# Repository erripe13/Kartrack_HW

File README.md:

# Kartrak – Hardware

> **Dépôts associés** :  
> - [Kartrack_SW](https://github.com/erripe13/Kartrack_SW) – Code embarqué STM32 (FreeRTOS, GPS, LoRa, SD...)  
> - [Kartrack_HW](https://github.com/erripe13/Kartrack_HW) – **Ce dépôt** – Schéma et PCB du système  
> - [Kartrack_APP](https://github.com/erripe13/Kartrack_APP) – Application d’analyse et visualisation des données

## Présentation du projet Kartrak

Kartrak est un système embarqué de chronométrage et de télémétrie pour karting, conçu pour être fixé sur le volant. Il enregistre en temps réel les données de course (position GPS, accélérations, orientation) et les transmet en LoRa à l'appli desktop et les enregistre sur carte microSD. L’objectif est de proposer un outil complet pour les pilotes amateurs ou en compétition : analyse post-course, visualisation en temps réel par l'équipe, appel aux stands, comparaisons de trajectoires.

---

Le projet est basé sur la plateforme **STM32F746G-DISCO**, exploitant son STM32 puissant et ses périphériques avancés (écran TFT, SDMMC, i2c, SPI, UART) pour accélérer le développement hardware, éliminant l'étape d'implémentation écran/uC.

Ce dépôt contient les fichiers **KiCad** du schéma électronique et du circuit imprimé (PCB) conçu pour le système embarqué Kartrack. Il s’agit d’une carte d’interface et d’alimentation destinée à supporter la carte **STM32F746G-DISCO** tout en intégrant les composants spécifiques au projet.

Le système est alimenté à partir de **deux batteries 18650** montées en **parallèle**. Un **convertisseur boost (step-up)** élève la tension à 5 V pour alimenter la carte STM32F7 Discovery via ses broches VIN (arduino) et GND. Ces 5V sont réutilisés et abaissés à 3.3V avec un LDO. Un autre LDO permet la recharge des batteries.

Le PCB a été conçu dans une logique de prototypage rapide :
- **Réduction du temps de conception** en réutilisant une carte STM32 existante (la DISCO) plutôt qu’un microcontrôleur nu.
- Embarque les modules suivants :
  - LoRa : RA-01 (SPI). Le Lora nous permet de couvrir un grand espace de communication (Piste de Karting) sans passer par le réseau GSM et a aussi l'a avantage d'une faible consommation électrique.
  - GPS : Quectel L76 (UART). Le grand avantage de ce GPS est sa fréquence élevée d'acquisition, ici 5Hz. La norme des GPS est de 1Hz, mais pour un kart à 60km/h sur une piste de 1000m la norme n'est pas suffisante.
  - IMU : ICM-42605 (I²C). L'accéléromètre et le gyroscope nous permettent d'ajouter une donnée en plus à notre pilote. Ici le gyro est réglé sur la mesure la plus rapide, et l'accélaration la plus élevée (16G). En cas d'accident par exemple cette donnée peut être des plus intéressantes.  
     
---

## À venir

- Intégration directe d’un STM32 nu sur une version 1 de ce projet, considérant celle-ci comme une bêta ou un POC.
- Création d'un boîtier en conséquence plus fin et plus petit, potentiellement étanche.
- Amélioration de la partie RF pour une meilleure fiabilité du GPS et une plus grande portée du LoRa.

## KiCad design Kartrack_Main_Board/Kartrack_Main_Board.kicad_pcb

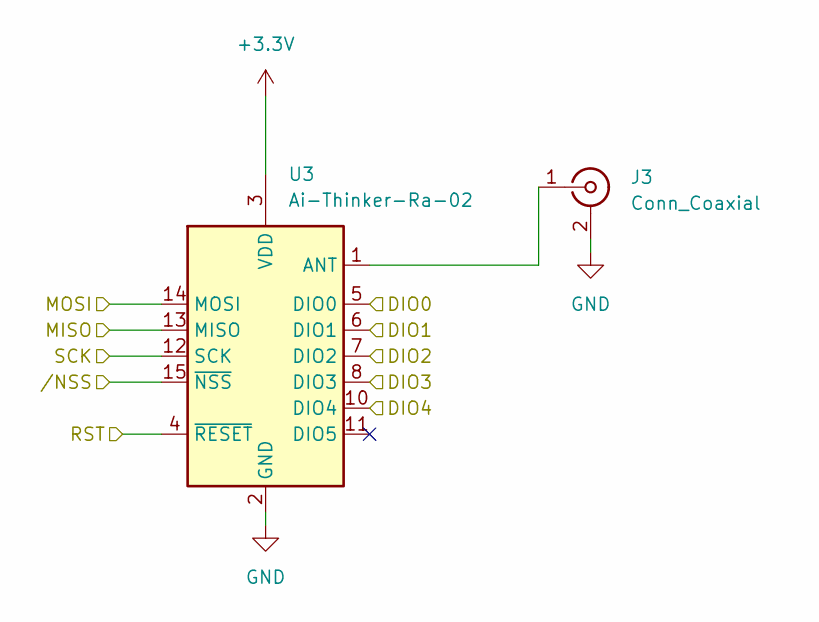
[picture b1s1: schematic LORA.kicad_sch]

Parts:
J3: Conn_Coaxial; U.FL_Molex_MCRF_73412-0110_Vertical
U3: Ai-Thinker-Ra-02; Ai-Thinker-Ra-01-LoRa

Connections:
+3.3V: U3.3 (VDD); also elsewhere on the board
/CONN/PA8: U3.8 (DIO3); also elsewhere on the board
/CONN/PA15: U3.7 (DIO2); also elsewhere on the board
/CONN/PB4: U3.10 (DIO4); also elsewhere on the board
/CONN/PB14_SPI2_MISO: U3.13 (MISO); also elsewhere on the board
/CONN/PB15_SPI2_MOSI: U3.14 (MOSI); also elsewhere on the board
/CONN/PF8_LORA_RST: U3.4 (~RESET); also elsewhere on the board
/CONN/PI1_SPI2_SCK: U3.12 (SCK); also elsewhere on the board
/CONN/PI2: U3.6 (DIO1); also elsewhere on the board
/CONN/PI3: U3.5 (DIO0); also elsewhere on the board
/CONN/PIO_SPI2_NSS: U3.15 (~NSS); also elsewhere on the board
GND: J3.2 (Ext), U3.2 (GND), U3.9 (GND), U3.16 (GND); also elsewhere on the board
unnamed: J3.1 (In), U3.1 (ANT)

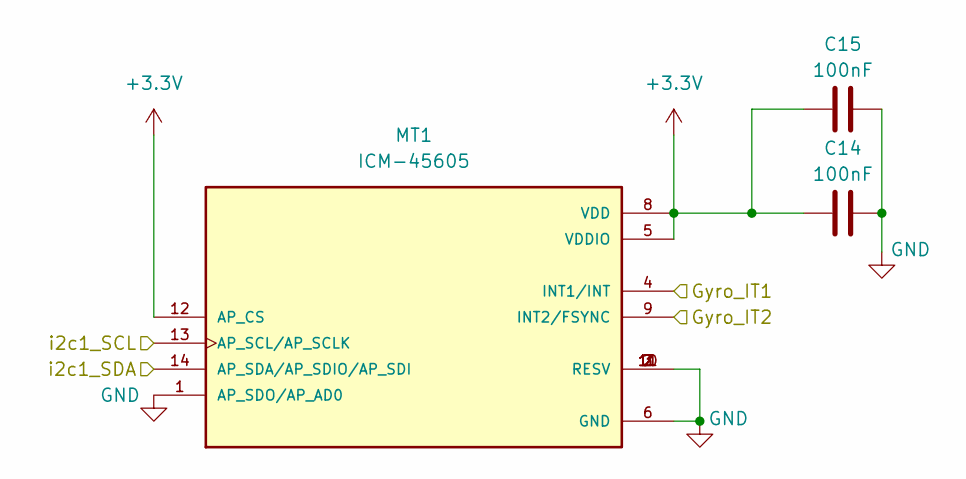
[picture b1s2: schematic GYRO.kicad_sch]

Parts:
C14, C15: 100nF; C_0402_1005Metric
MT1: ICM-45605; IC_ICM-45605; PARTREV 1.7

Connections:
+3.3V: C14.1, C15.1, MT1.5 (VDDIO), MT1.8 (VDD), MT1.12 (AP_CS); also elsewhere on the board
/CONN/PB8_SCL: MT1.13 (AP_SCL/AP_SCLK); also elsewhere on the board
/CONN/PB9_SDA: MT1.14 (AP_SDA/AP_SDIO/AP_SDI); also elsewhere on the board
/CONN/PF6: MT1.9 (INT2/FSYNC); also elsewhere on the board
/CONN/PG7: MT1.4 (INT1/INT); also elsewhere on the board
GND: C14.2, C15.2, MT1.1 (AP_SDO/AP_AD0), MT1.2 (RESV), MT1.3 (RESV), MT1.6 (GND), MT1.7 (RESV), MT1.10 (RESV), MT1.11 (RESV); also elsewhere on the board

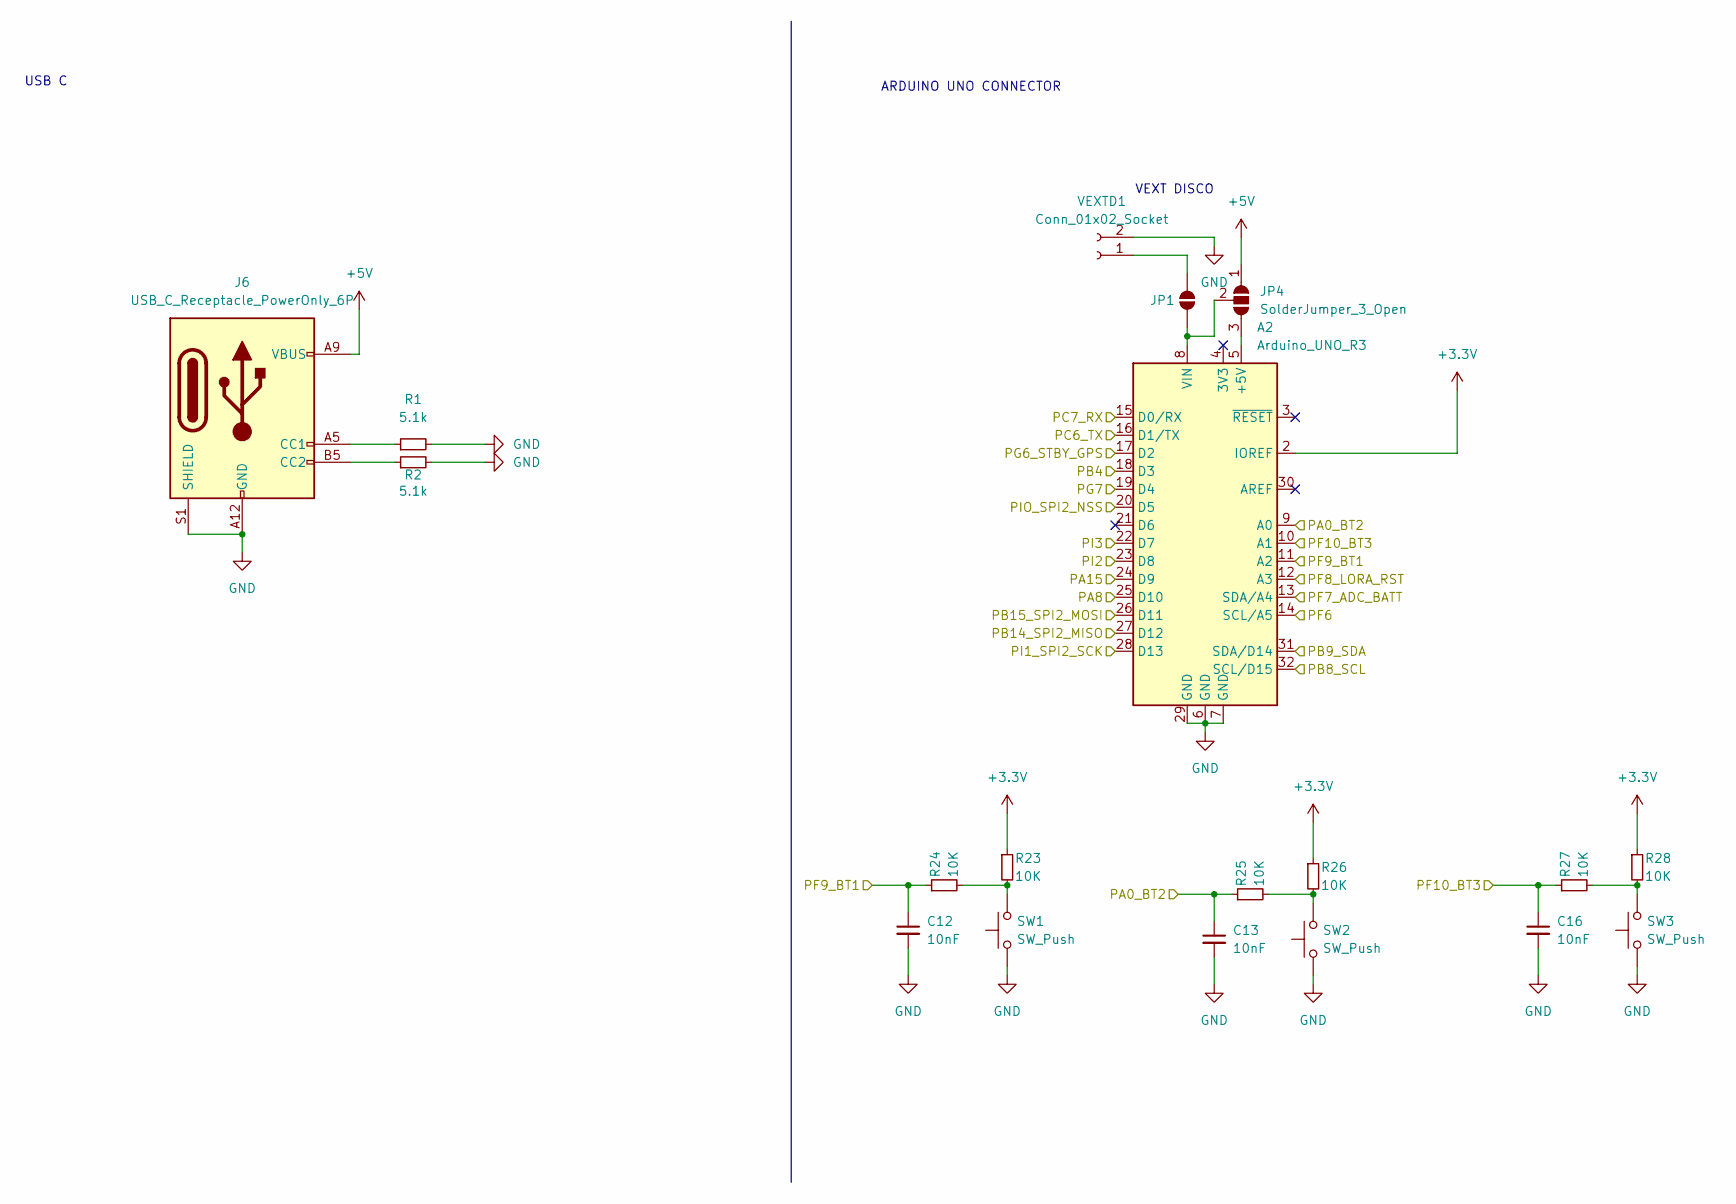
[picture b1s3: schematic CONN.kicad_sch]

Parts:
A2: Arduino_UNO_R3
C12, C13, C16: 10nF; C_0603_1608Metric
J6: USB_C_Receptacle_PowerOnly_6P; USB_C_Receptacle_GCT_USB4125-xx-x_6P_TopMnt_Horizontal
JP1: SolderJumper_2_Open; SolderJumper-2_P1.3mm_Open_RoundedPad1.0x1.5mm
JP4: SolderJumper_3_Open; SolderJumper-3_P2.0mm_Open_TrianglePad1.0x1.5mm_NumberLabels
R1, R2: 5.1k; R_0603_1608Metric
R23, R24, R25, R26, R27, R28: 10K; R_0603_1608Metric
SW1, SW2, SW3: SW_Push; JST_PH_S2B-PH-K_1x02_P2.00mm_Horizontal
VEXTD1: Conn_01x02_Socket; PhoenixContact_MC_1,5_2-G-3.81_1x02_P3.81mm_Horizontal

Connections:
+3.3V: A2.2 (IOREF), R23.1, R26.1, R28.1; also elsewhere on the board
+5V: J6.A9 (VBUS), J6.B9 (VBUS), JP4.1 (A); also elsewhere on the board
/ALIM/ADC_VBATT: A2.13 (SDA/A4); also elsewhere on the board
/CONN/PA0_BT2: A2.9 (A0), C13.1, R25.1
/CONN/PA8: A2.25 (D10); also elsewhere on the board
/CONN/PA15: A2.24 (D9); also elsewhere on the board
/CONN/PB4: A2.18 (D3); also elsewhere on the board
/CONN/PB8_SCL: A2.32 (SCL/D15); also elsewhere on the board
/CONN/PB9_SDA: A2.31 (SDA/D14); also elsewhere on the board
/CONN/PB14_SPI2_MISO: A2.27 (D12); also elsewhere on the board
/CONN/PB15_SPI2_MOSI: A2.26 (D11); also elsewhere on the board
/CONN/PC6_TX: A2.16 (D1/TX); also elsewhere on the board
/CONN/PC7_RX: A2.15 (D0/RX); also elsewhere on the board
/CONN/PF6: A2.14 (SCL/A5); also elsewhere on the board
/CONN/PF8_LORA_RST: A2.12 (A3); also elsewhere on the board
/CONN/PF9_BT1: A2.11 (A2), C12.1, R24.1
/CONN/PF10_BT3: A2.10 (A1), C16.1, R27.1
/CONN/PG6_STBY_GPS: A2.17 (D2); also elsewhere on the board
/CONN/PG7: A2.19 (D4); also elsewhere on the board
/CONN/PI1_SPI2_SCK: A2.28 (D13); also elsewhere on the board
/CONN/PI2: A2.23 (D8); also elsewhere on the board
/CONN/PI3: A2.22 (D7); also elsewhere on the board
/CONN/PIO_SPI2_NSS: A2.20 (D5); also elsewhere on the board
GND: A2.6 (GND), A2.7 (GND), A2.29 (GND), C12.2, C13.2, C16.2, J6.A12 (GND), J6.B12 (GND), J6.S1 (SHIELD), R1.2, R2.2, SW1.1, SW2.1, SW3.1, VEXTD1.2; also elsewhere on the board
unnamed: A2.5 (+5V), JP4.3 (B)
unnamed: A2.8 (VIN), JP1.1 (A), JP4.2 (C)
unnamed: J6.A5 (CC1), R1.1
unnamed: J6.B5 (CC2), R2.1
unnamed: JP1.2 (B), VEXTD1.1
unnamed: R23.2, R24.2, SW1.2
unnamed: R25.2, R26.2, SW2.2
unnamed: R27.2, R28.2, SW3.2

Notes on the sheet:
USB C
ARDUINO UNO CONNECTOR
VEXT DISCO

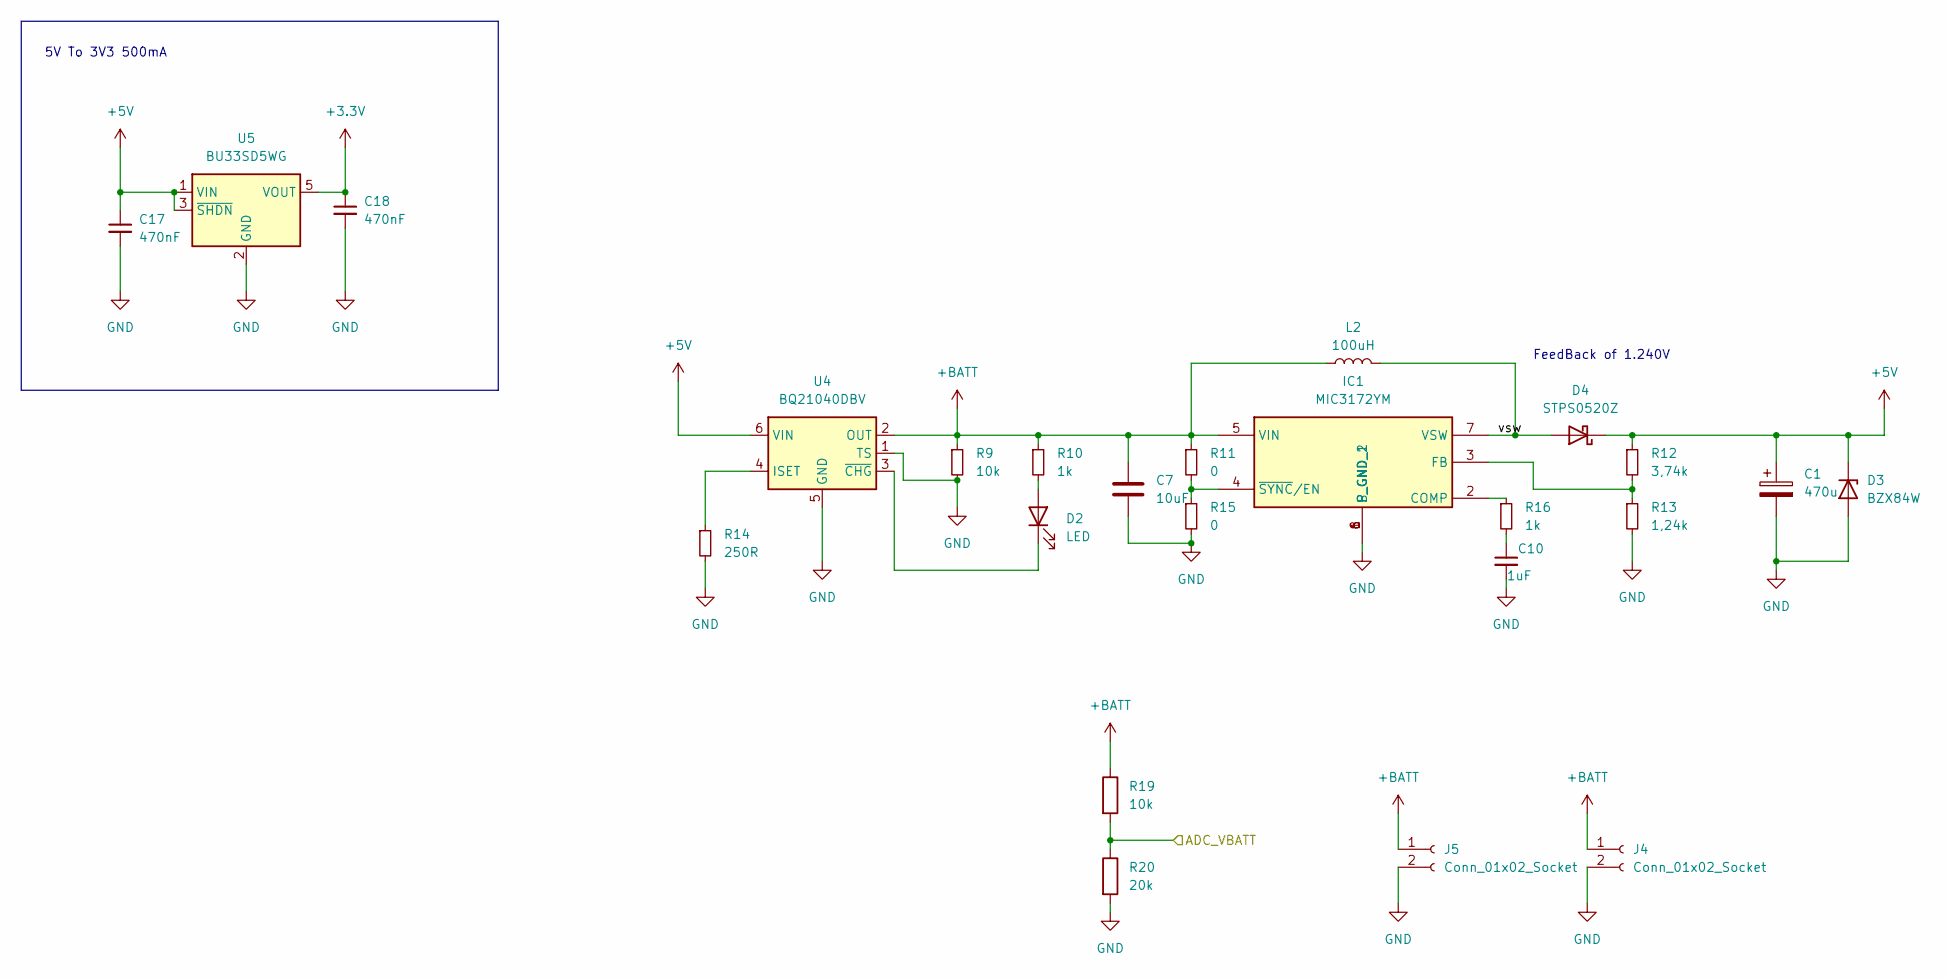
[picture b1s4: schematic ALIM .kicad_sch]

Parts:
C1: 470u; CP_Elec_8x10
C7: 10uF; C_0603_1608Metric
C10: 1uF; C_0603_1608Metric
C17, C18: 470nF; C_0603_1608Metric
D2: LED; LED_0603_1608Metric
D3: BZX84W; SOT-23
D4: STPS0520Z; D_SOD-123
IC1: MIC3172YM; SOIC127P599X173-8N; MPN MIC3172YM; Mouser Part Number 998-MIC3172YM
J4, J5: Conn_01x02_Socket; BatteryHolder_MPD_BH-18650-PC2
L2: 100uH; L_12x12mm_H8mm
R9, R19: 10k; R_0603_1608Metric
R10, R16: 1k; R_0603_1608Metric
R11, R15: 0; R_0603_1608Metric
R12: 3,74k; R_0603_1608Metric; MPN CRCW06033K74DHEAP
R13: 1,24k; R_0603_1608Metric; MPN CRCW06031K24FKEAHP
R14: 250R; R_0603_1608Metric
R20: 20k; R_0603_1608Metric
U4: BQ21040DBV; SOT-23-6; MPN BQ21040DBVR
U5: BU33SD5WG; SOT-23-5; MPN BU33SD5WG-TR

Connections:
+3.3V: C18.1, U5.5 (VOUT); also elsewhere on the board
+5V: C1.1, C17.1, D3.3 (K), D4.1 (K), R12.1, U4.6 (VIN), U5.1 (VIN), U5.3 (~SHDN); also elsewhere on the board
+BATT: C7.1, IC1.5 (VIN), J4.1, J5.1, L2.1, R9.1, R10.1, R11.1, R19.1, U4.2 (OUT)
/ALIM/ADC_VBATT: R19.2, R20.1; also elsewhere on the board
/ALIM/vsw: D4.2 (A), IC1.7 (VSW), L2.2
GND: C1.2, C7.2, C10.2, C17.2, C18.2, D3.1 (A), IC1.1 (S_GND), IC1.6 (P_GND_2), IC1.8 (P_GND_1), J4.2, J5.2, R9.2, R13.2, R14.2, R15.2, R20.2, U4.1 (TS), U4.5 (GND), U5.2 (GND); also elsewhere on the board
unnamed: C10.1, R16.2
unnamed: D2.2 (A), R10.2
unnamed: D2.1 (K), U4.3 (~CHG)
unnamed: IC1.2 (COMP), R16.1
unnamed: IC1.3 (FB), R12.2, R13.1
unnamed: IC1.4 (~SYNC/EN), R11.2, R15.1
unnamed: R14.1, U4.4 (ISET)

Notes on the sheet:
5V To 3V3 500mA
FeedBack of 1.240V

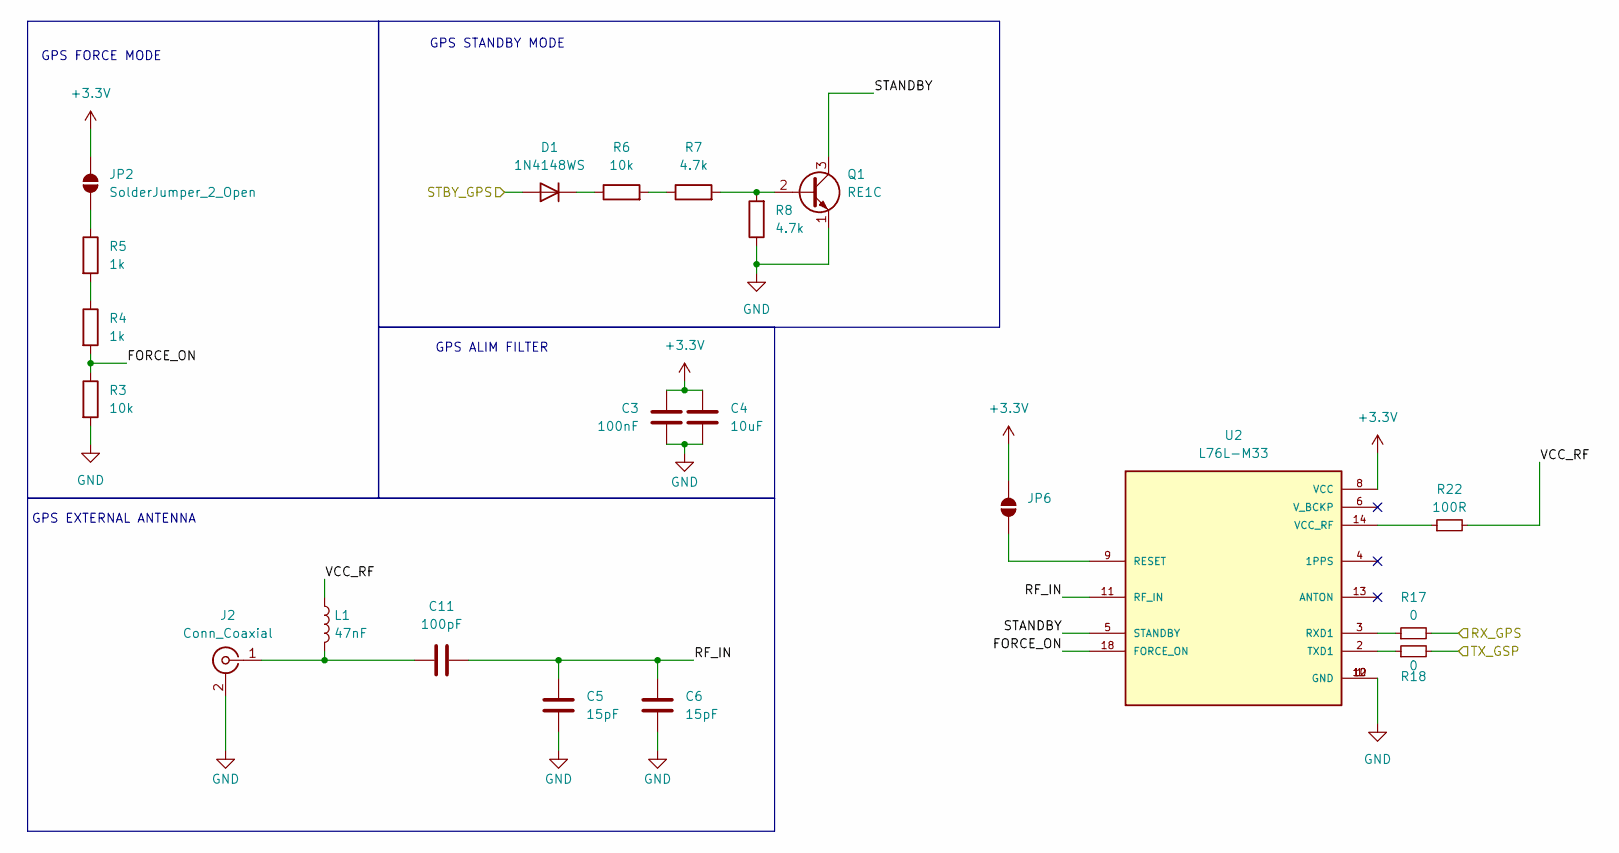
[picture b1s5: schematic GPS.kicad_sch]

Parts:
C3: 100nF; C_0603_1608Metric
C4: 10uF; C_0603_1608Metric
C5, C6: 15pF; C_0603_1608Metric
C11: 100pF; C_0603_1608Metric
D1: 1N4148WS; D_SOD-323
J2: Conn_Coaxial; U.FL_Molex_MCRF_73412-0110_Vertical
JP2, JP6: SolderJumper_2_Open; SolderJumper-2_P1.3mm_Open_RoundedPad1.0x1.5mm
L1: 47nF; L_0603_1608Metric
Q1: RE1C; SOT-416
R3, R6: 10k; R_0603_1608Metric
R4, R5: 1k; R_0603_1608Metric
R7, R8: 4.7k; R_0603_1608Metric
R17, R18: 0; R_0603_1608Metric
R22: 100R; R_0603_1608Metric
U2: L76L-M33; XCVR_L76L-M33; DigiKey_Part_Number 2958-L76L-M33TR-ND

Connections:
+3.3V: C3.1, C4.1, JP2.2 (B), JP6.2 (B), U2.8 (VCC); also elsewhere on the board
/CONN/PC6_TX: R17.2; also elsewhere on the board
/CONN/PC7_RX: R18.2; also elsewhere on the board
/CONN/PG6_STBY_GPS: D1.2 (A); also elsewhere on the board
/GPS/FORCE_ON: R3.1, R4.2, U2.18 (FORCE_ON)
/GPS/RF_IN: C5.1, C6.1, C11.2, U2.11 (RF_IN)
/GPS/STANDBY: Q1.3 (C), U2.5 (STANDBY)
/GPS/VCC_RF: L1.1, R22.2
GND: C3.2, C4.2, C5.2, C6.2, J2.2 (Ext), Q1.1 (E), R3.2, R8.1, U2.1 (GND), U2.10 (GND), U2.12 (GND); also elsewhere on the board
unnamed: D1.1 (K), R6.1
unnamed: C11.1, J2.1 (In), L1.2
unnamed: JP2.1 (A), R5.1
unnamed: JP6.1 (A), U2.9 (RESET)
unnamed: Q1.2 (B), R7.2, R8.2
unnamed: R4.1, R5.2
unnamed: R6.2, R7.1
unnamed: R17.1, U2.3 (RXD1)
unnamed: R18.1, U2.2 (TXD1)
unnamed: R22.1, U2.14 (VCC_RF)

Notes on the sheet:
GPS EXTERNAL ANTENNA
GPS STANDBY MODE
GPS ALIM FILTER
GPS FORCE MODE

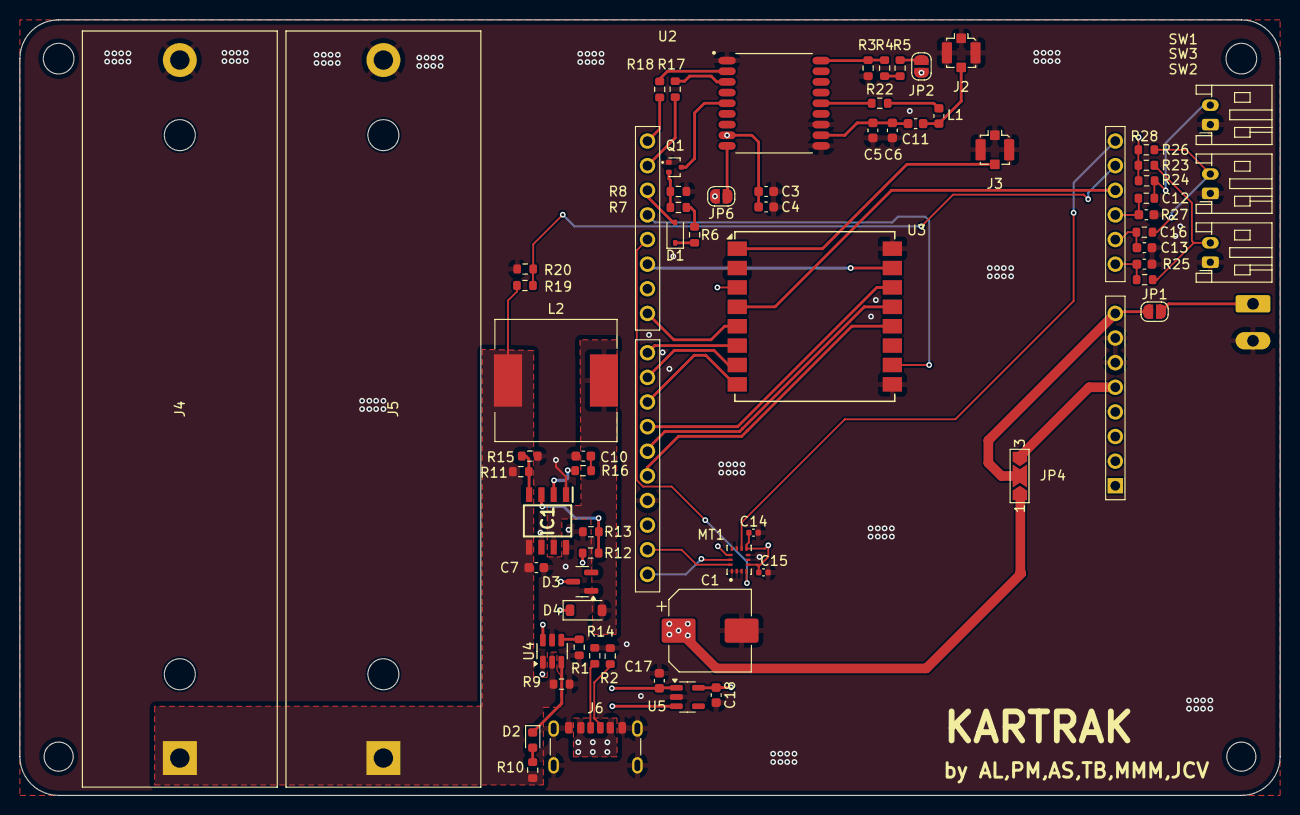
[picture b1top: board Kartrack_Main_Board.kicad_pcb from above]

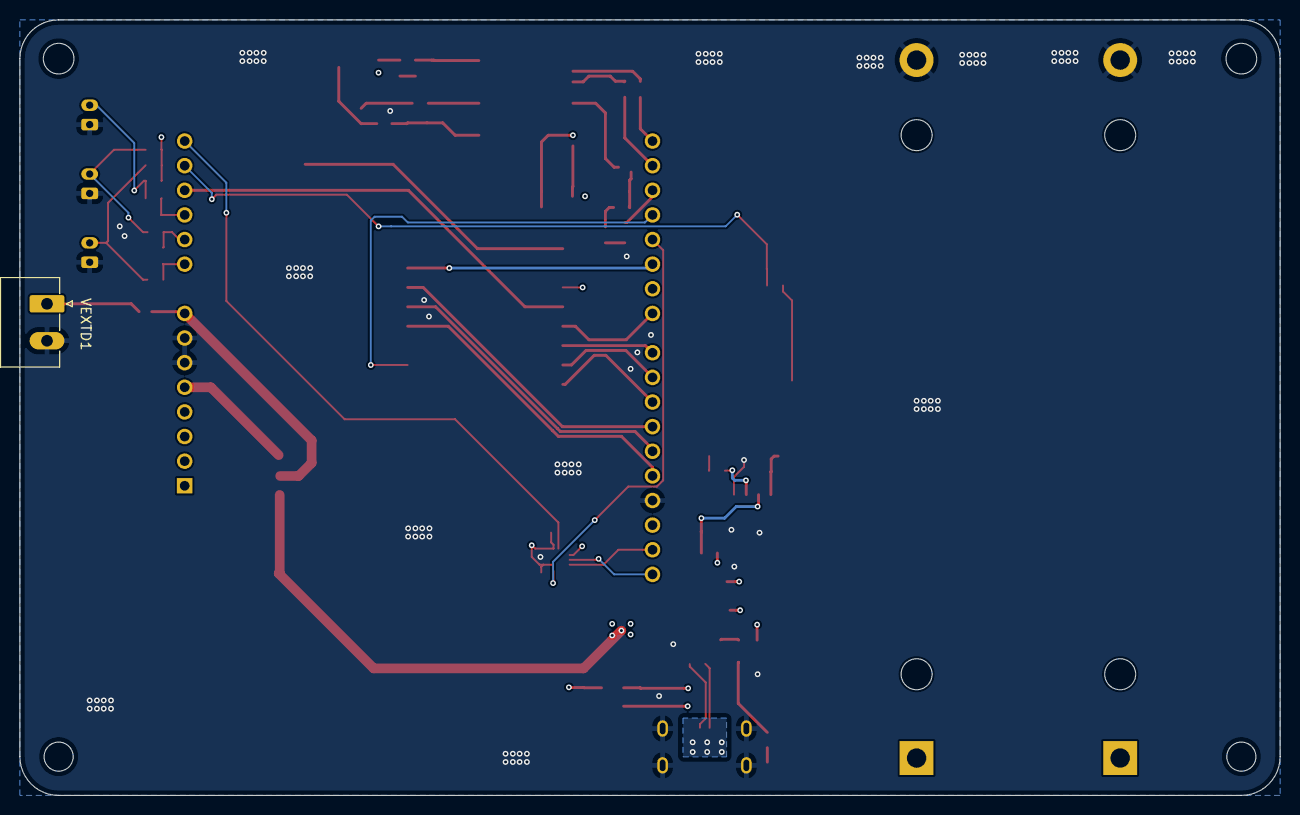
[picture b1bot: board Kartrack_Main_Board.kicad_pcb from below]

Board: 4 copper layers, 130.0 x 80.0 mm, 69 parts (2 on the bottom side), 56 nets.

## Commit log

2025-03-14 Project Creation
2025-03-14 add datasheet
2025-03-14 arduino footprint
2025-03-14 arduino layout
2025-03-21 connector
2025-03-21 add MIC
2025-03-21 schematic GPS
2025-03-21 added power IC datasheet
2025-03-21 Schematic
2025-03-21 FIn de séance
2025-03-26 buck schematic
2025-03-27 buck verif
2025-03-28 BLOC schematic
2025-03-28 ajouts des boutons
2025-03-28 added connectors for pulldown pushbuttons
2025-03-28 add filtering button
2025-03-28 SCHEMATIC FINISHED
2025-03-28 PCB early
2025-03-28 update Alim
2025-03-29 Routing alim
2025-04-03 PCB V1
2025-04-03 run drc
2025-04-03 add adc batt
2025-04-03 meca update
2025-04-04 pcb via in pad remove
2025-04-04 kartrack logo
2025-04-04 Alim jumper
2025-04-04 production files
2025-06-11 mechanical update & datasheet
2025-06-11 pré-version README.md
